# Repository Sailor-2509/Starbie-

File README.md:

I started by my project by adding the components in the schematic editor and and then connected them
 And Started assigning the footprints then in the pcb editor i arranged the components and wired them

Then i view in 3D and made a box around it with edge cuts so that the pcb is small and compact and in the last it was complete in all respect

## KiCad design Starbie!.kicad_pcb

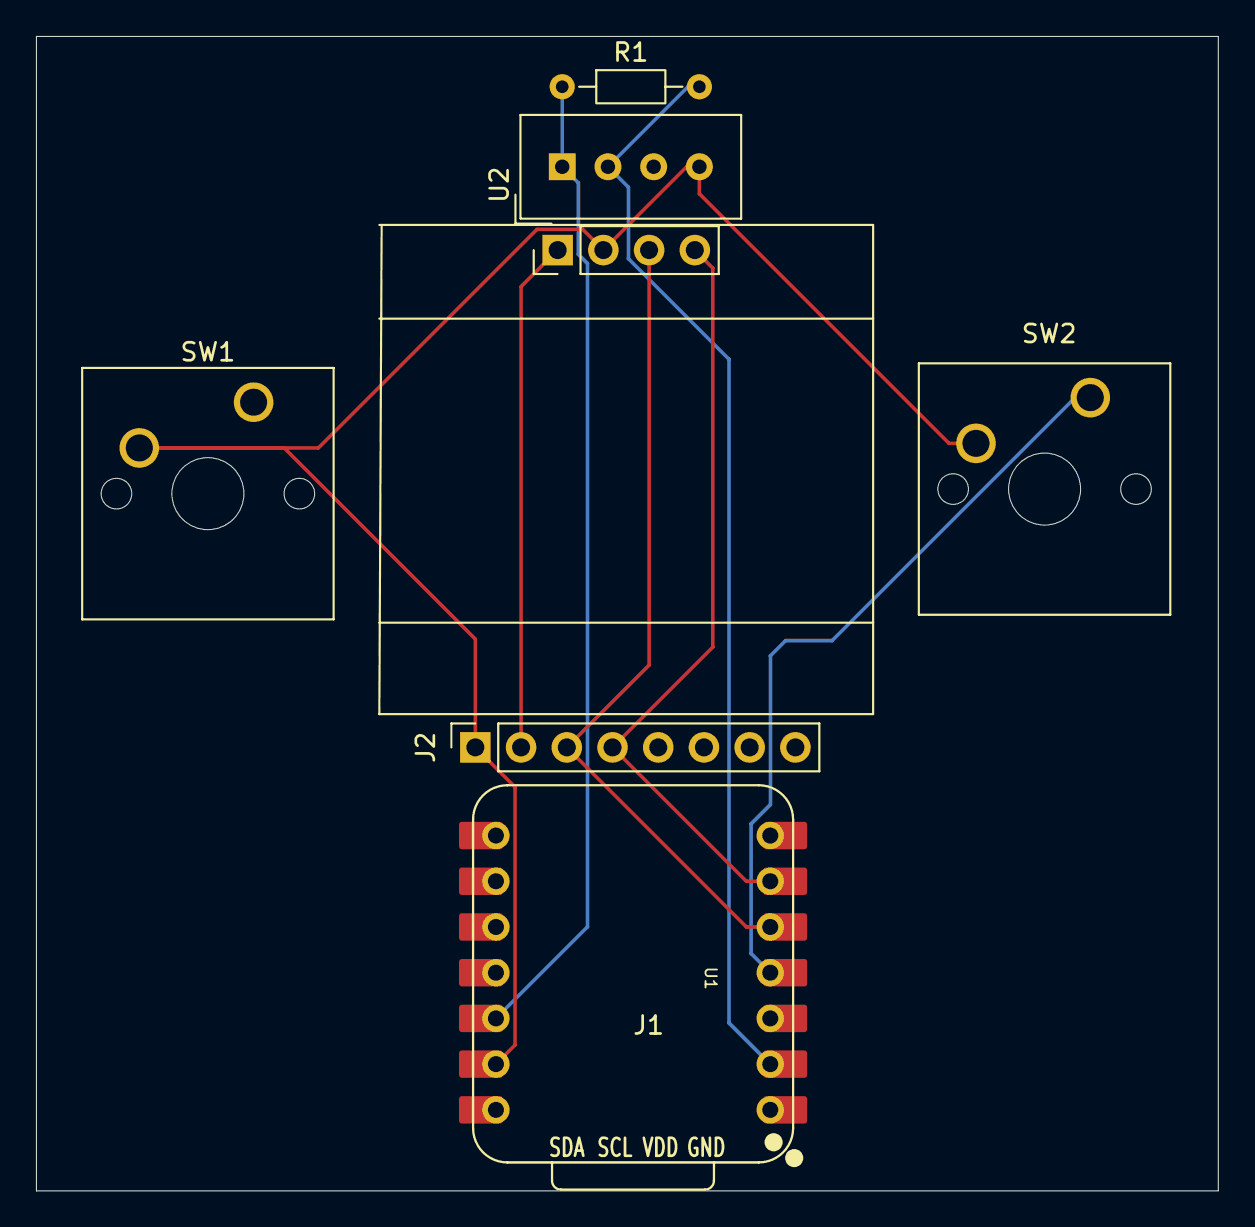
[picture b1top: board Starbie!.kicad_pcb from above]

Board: 2 copper layers, 65.7 x 64.1 mm, 7 parts (0 on the bottom side), 7 nets.

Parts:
J1: Conn_01x08_Pin; Display_128x64_096_I2C
J2: Conn_01x04_Pin; PinSocket_1x08_P2.54mm_Vertical
R1: 10K; R_Axial_DIN0204_L3.6mm_D1.6mm_P7.62mm_Horizontal
SW1, SW2: SW_Push; SW_Cherry_MX_1.00u_PCB
U1: XIAO-ESP32-C3-SMD; XIAO-ESP32-C6-DIP
U2: DHT11; Aosong_DHT11_5.5x12.0_P2.54mm

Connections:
+3.3V: R1.1, U1.12 (3V3_OUT), U2.1 (VDD)
+3V3: J1.1, J2.2
/DHT11 DATA: R1.2, U1.2 (D1), U2.2 (DATA)
/GPIO3: SW2.1, U1.4 (D3)
/SCL: J1.3, J2.3, U1.5 (D4)
/SDA: J1.4, J2.4, U1.6 (D5)
GND: J1.2, J2.1, SW1.2, SW2.2, U1.13 (GND), U2.4 (GND)
